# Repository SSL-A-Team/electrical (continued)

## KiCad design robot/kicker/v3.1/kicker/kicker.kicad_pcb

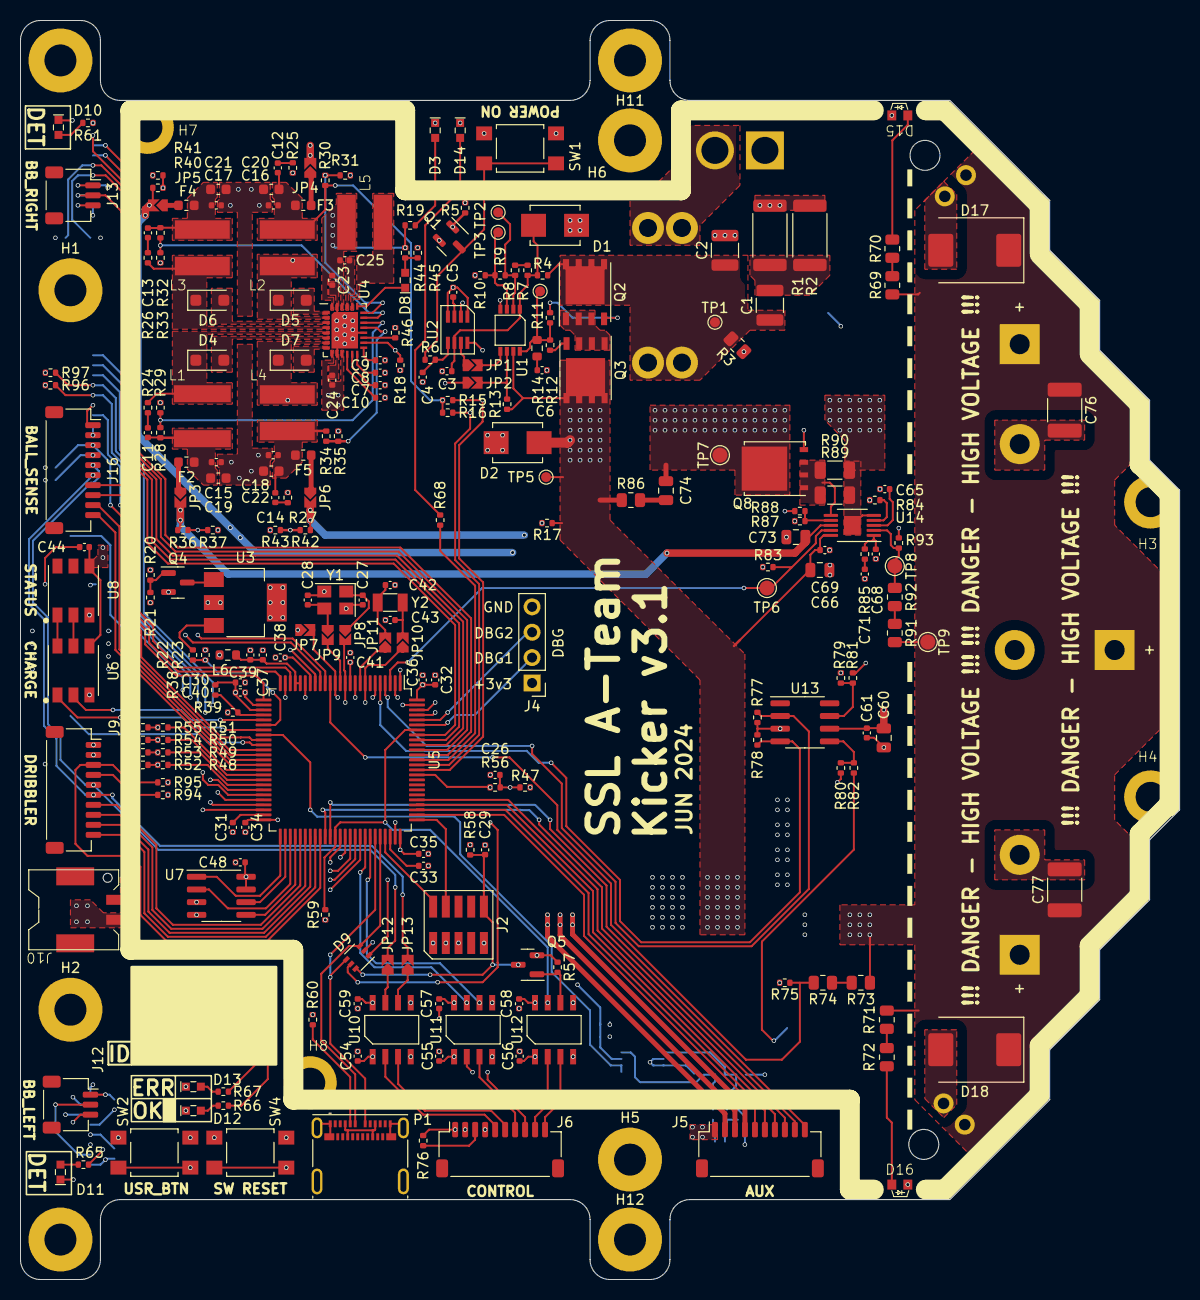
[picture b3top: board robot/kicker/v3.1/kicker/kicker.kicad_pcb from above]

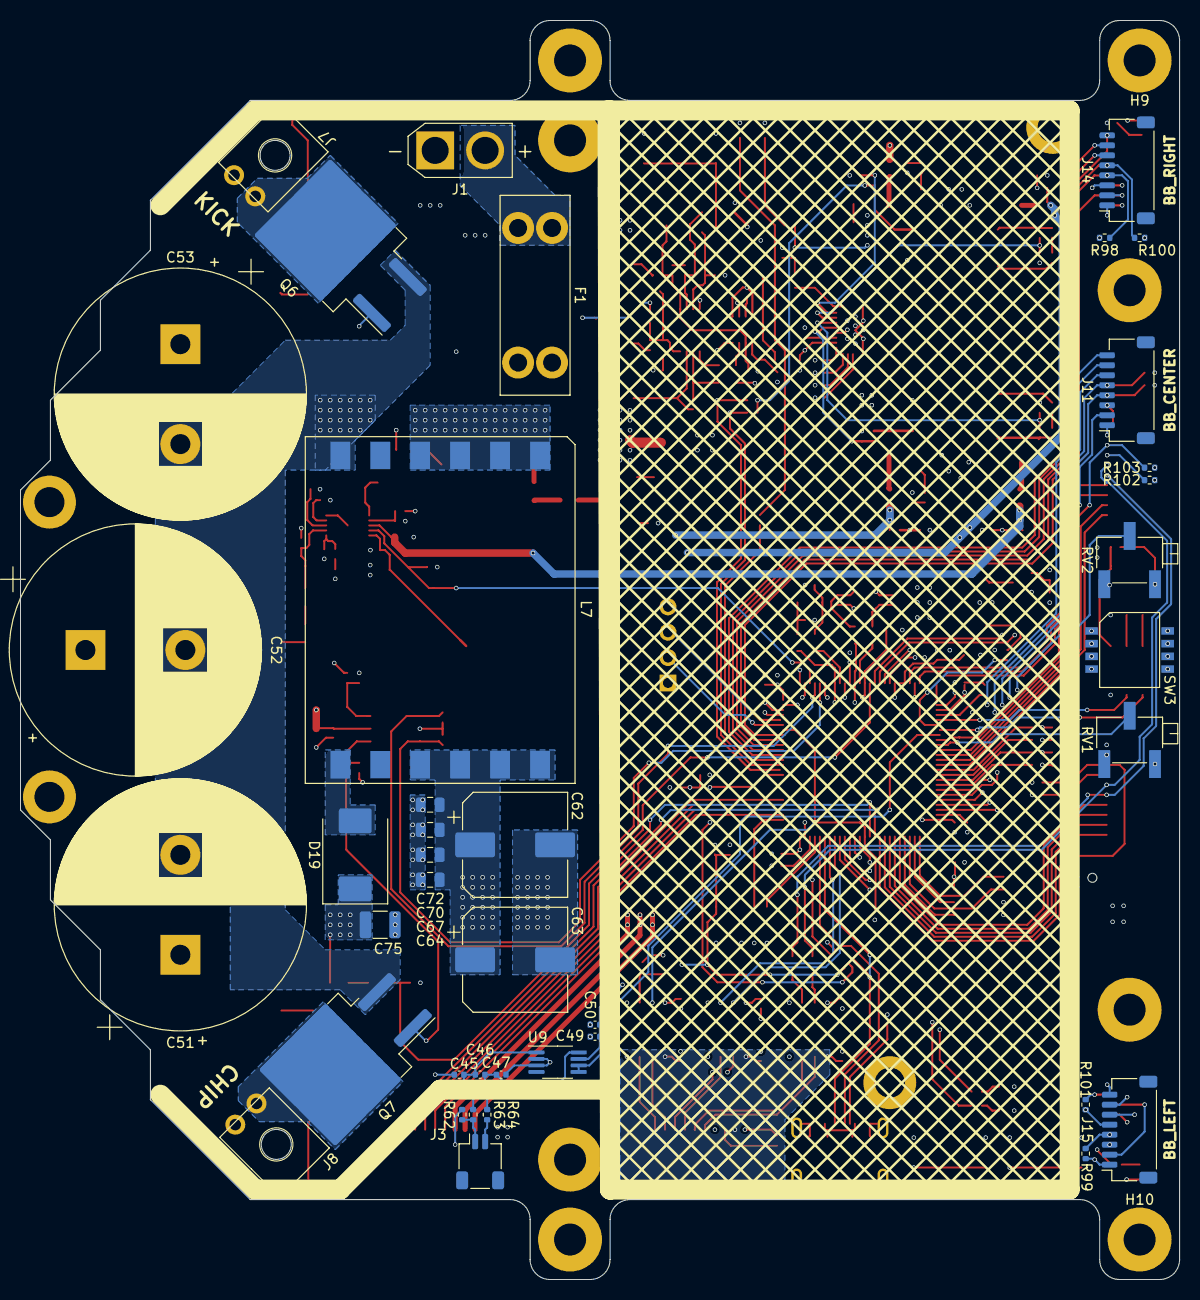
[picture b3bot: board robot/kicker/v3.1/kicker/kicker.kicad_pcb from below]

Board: 6 copper layers, 116.0 x 126.0 mm, 292 parts (40 on the bottom side), 203 nets.

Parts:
C1: 10u 100V; C_1210_3225Metric
C2: 10u 63V; C_1210_3225Metric
C3, C4, C5, C26, C29, C34, C35, C36, C37, C38, C40, C41, C46, C48, C49, C54, C55, C56, C57, C58, C59, C61, C68, C69: 100n 50V; C_0402_1005Metric
C6: 4.7n 63V; C_0402_1005Metric
C7, C8, C45, C47: 10n 6.3V; C_0402_1005Metric
C9, C10: 470n 6.3V; C_0402_1005Metric
C11, C12, C13, C14: 1n 50V; C_0402_1005Metric
C15, C16, C17, C18, C23, C24, C25, C39: 1u 50V; C_0402_1005Metric
C19, C20, C21, C22: 10u 25V; C_0603_1608Metric
C27, C28: 11pF; C_0402_1005Metric
C30, C31, C32, C33, C44: 4.7u 6.3V; C_0402_1005Metric
C42, C43: 15pF; C_0402_1005Metric
C50: 10u 6.3V; C_0402_1005Metric
C51, C52, C53: 1000uF 200V; CP_Radial_D25.0mm_P10.00mm_SnapIn
C60, C64, C66, C67, C70, C72: 10u 50V; C_0805_2012Metric
C62, C63: 220u 50V; CP_Elec_10x10
C65: 10n 50V; C_0402_1005Metric
C71: 6.8n 50V; C_0402_1005Metric
C73: 4.7u 50V; C_0805_2012Metric
C74: 100n 200V; C_0805_2012Metric
C75: 100n 500V; C_1210_3225Metric
C76, C77: 470n 500V; C_1812_4532Metric
D1, D2: 824521261; D_SMB_Non-Polar
D3: XL-1608UWC-04; LED0603
D4, D5, D6, D7: DSS14U; D_SOD-123F
D8, D13: Red; LED0603
D9: PESD3V3L5UY; SOT-363_SC-70-6
D10, D11: Blue; LED0603
D12: Green; LED0603
D14: XL-1608UOC-06; LED0603
D15, D16: Red; APA1606
D17, D18: MURS460; D_SMC
D19: HS5M; D_SMC
F1: 15A; 3557-2
F2, F3, F4, F5: 1.0A; Fuse_0603_1608Metric
H1, H2, H5, H6, H9, H10, H11, H12: M3; MountingHole_3.2mm_M3_Pad
H3, H4, H7, H8: 9774005243R; WE-9774005243R
J1: XT30-F; AMASS_XT30U-M_1x02_P5.0mm_Vertical
J2: Conn_ARM_JTAG_SWD_10; Samtec-2x5pin-0.5mm
J3: Conn_01x02; JST_SH_SM02B-SRSS-TB_1x02-1MP_P1.00mm_Horizontal
J4: Conn_01x04_Pin; PinHeader_1x04_P2.54mm_Vertical
J5, J6, J9, J16: Conn_01x10; JST_SH_SM10B-SRSS-TB_1x10-1MP_P1.00mm_Horizontal
J7, J8: Conn_01x02; 2157601002
J10: Conn_01x02; SM02B-PASS-TBT
J11, J14, J15: Conn_01x08; JST_SH_SM08B-SRSS-TB_1x08-1MP_P1.00mm_Horizontal
J12, J13: Conn_01x03; JST_SH_SM03B-SRSS-TB_1x03-1MP_P1.00mm_Horizontal
JP1: BTN_EN; SolderJumper-2_2.0x1.2mm_Closed
JP2: PWR_EN; SolderJumper-2_2.0x1.2mm_Closed
JP3: 12v0 EN; SolderJumper-2_2.0x1.2mm_Open
JP4: 3v3 EN; SolderJumper-2_2.0x1.2mm_Open
JP5: 5v0 EN; SolderJumper-2_2.0x1.2mm_Open
JP6: 6v2 EN; SolderJumper-2_2.0x1.2mm_Open
JP7: Disable Micro; SolderJumper-2_2.0x1.2mm_Open
JP8, JP9: 8MHZ_CLK_LOCAL; SolderJumper-2_2.0x1.2mm_Closed
JP10, JP11: 32KHZ_CLK_LOCAL; SolderJumper-2_2.0x1.2mm_Closed
JP12: 8MHZ_CLK_EXT; SolderJumper-2_2.0x1.2mm_Closed
JP13: 32KHZ_CLK_EXT; SolderJumper-2_2.0x1.2mm_Closed
L1: ASPI-6045S-220M-T; ASPI-6045S
L2, L3, L4, L5: SDCHA1V5040-150-R; SDCHA1V50
L6: 650 @100MHz; R_0603_1608Metric
L7: GA3460-BL; GA34XX-BL
P1: USB_C_Plug_USB2.0; USB_C_Receptacle_Molex_105450-0101
Q1: BSS138; SOT-23
Q2, Q3: SQJA80EP-T1_GE3; PowerPAK_SO-8L_Single
Q4: SI2310-TP; SOT-23
Q5: BSS138K; SOT-23
Q6, Q7: IXGA48N60A3; TO-263-2
Q8: BSC0402NSATMA1; TDSON-8-1
R1, R2: 1; R_2512_6332Metric
R3, R69, R70, R71, R72: 1.47M; R_0805_2012Metric
R4, R6, R83: 1k; R_0402_1005Metric
R5, R13, R23, R47, R52, R53, R54, R55, R58, R59, R61, R63, R64, R65, R66, R67, R68, R77, R78, R94, R95, R102, R103: 10k; R_0402_1005Metric
R7: 10M; R_0402_1005Metric
R8, R15, R16: 1.5M; R_0402_1005Metric
R9: 69.8k; R_0402_1005Metric
R10: 232k; R_0402_1005Metric
R11, R12, R20, R81, R82, R88: 10; R_0402_1005Metric
R14: 5.1k; R_0603_1608Metric
R17, R18, R57, R79, R80, R87: 100k; R_0402_1005Metric
R19, R38: 23.2k 1%; R_0402_1005Metric
R21: 4.7k; R_0402_1005Metric
R22: 210k; R_0402_1005Metric
R24, R25, R26, R27: 1k 1%; R_0402_1005Metric
R28, R84: 140k 1%; R_0402_1005Metric
R29, R31, R33, R35, R37, R39, R41, R43: 10k 1%; R_0402_1005Metric
R30: 31.6k 1%; R_0402_1005Metric
R32: 53.6k 1%; R_0402_1005Metric
R34: 68.1k 1%; R_0402_1005Metric
R36: 110k 1%; R_0402_1005Metric
R40: 40.2k 1%; R_0402_1005Metric
R42: 52.3k 1%; R_0402_1005Metric
R44, R45, R60: 5.1k; R_0402_1005Metric
R46: 10.7k 1%; R_0402_1005Metric
R48, R49, R50, R51, R56, R76: 330; R_0402_1005Metric
R62: 1M; R_0402_1005Metric
R73, R74: 475k; R_0805_2012Metric
R75: 4.75k; R_0402_1005Metric
R85: 22k 1%; R_0402_1005Metric
R86: 1; R_0805_2012Metric
R89, R90: 4m 1%; R_1206_3216Metric
R91, R92: 976k 0.1%; R_0805_2012Metric
R93: 17.4k 0.1%; R_0402_1005Metric
R96, R97, R98, R99, R100, R101: 2.1k; R_0402_1005Metric
RV1: ACFG1; Potentiometer_Bourns_3269X_Horizontal
RV2: ACFG2; Potentiometer_Bourns_3269X_Horizontal
SW1: PWR_ON; SW_SPST_TL3305A
SW2: BTN0; SW_SPST_TL3305A
SW3: SW_DIP_x04; CHP-041TB
SW4: RST; SW_SPST_TL3305A
TP1: VBatt EOS; TestPoint_Pad_D1.0mm
TP2: LTC4367 UV EOS; TestPoint_Pad_D1.0mm
TP3: LTC4367 OV EOS; TestPoint_Pad_D1.0mm
TP4: Gate SS; TestPoint_Pad_D1.0mm
TP5: VBatt Sys; TestPoint_Pad_D1.0mm
TP6: CHG_EN; TestPoint_Pad_D1.5mm
TP7: SPICE: V_{drain} <<<HIGH VOLTAGE>>>; TestPoint_Pad_D1.5mm
TP8: FB; TestPoint_Pad_D1.5mm
TP9: SPICE: V_{out} <<<HIGH VOLTAGE>>>; TestPoint_Pad_D1.5mm
U1: LTC4367; MS8
U2: LTC2955-1; LTC2955-TS8
U3: ITS4140N; SOT-223
U4: LT3504; UFD
U5: STM32F407VETx; LQFP-100_14x14mm_P0.5mm
U6, U8: SK9822
U7: AT25DF041x-UxN-x; SOIC-8_3.9x4.9mm_P1.27mm
U9: AD8494; MSOP-8_3x3mm_P0.65mm
U10, U12: ISO6720-Q1; ISO672X
U11: ISO6721-Q1; ISO672X
U13: IX4427; SOIC-8_3.9x4.9mm_P1.27mm
U14: LT3757EMSE; MSOP-10-1EP_3x3mm_P0.5mm_EP1.68x1.88mm
Y1: TAXM8M4RDBCCT2T; Crystal_SMD_3225-4Pin_3.2x2.5mm
Y2: Q13FC13500005; Crystal_SMD_3215-2Pin_3.2x1.5mm

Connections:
+3.3V_{PREFUSE}: C12.2, C16.1, C20.1, F3.1, L2.2, R15.1, R16.1, R30.1
+3V3: C30.2, C32.2, C34.1, C35.1, C36.1, C38.1, C40.1, C41.1, C48.2, C49.1, C50.2, C57.1, C58.1, C59.1, J2.1 (VTref), J4.1, J5.2, J9.2, J11.1, J12.1, J13.1, J14.1, J15.1, J16.2, JP4.2 (B), L6.1, R20.2, R38.1, R58.1, R94.1, R95.1, R96.1, R97.1, R98.1, R99.1, R100.1, R101.1, R102.1, R103.1, RV1.1, RV2.1, SW2.2, SW3.5, SW3.6, SW3.7, SW3.8, U5.6 (VBAT), U5.11 (VDD), U5.19 (VDD), U5.28 (VDD), U5.50 (VDD), U5.75 (VDD), U5.100 (VDD), U7.3 (~WP/IO2), U7.7 (~HOLD/IO3), U7.8 (VCC), U9.7 (+Vs), U10.8 (VCC2), U11.8 (VCC2), U12.8 (VCC2)
+5V: C44.2, J5.3, JP5.2 (B), R40.1, U6.4 (VCC), U8.4 (VCC)
+6V: J5.4, JP6.2 (B), R42.1
+12V: C60.1, C61.1, C73.1, JP3.2 (B), R36.1, U13.6 (V+), U14.8 (INTVCC)
+BATT: C23.1, C24.1, C25.2, C62.1, C63.1, C64.1, C66.1, C67.1, C69.1, C70.1, C72.1, D2.2 (A2), J10.1, L5.2, L7.9, L7.10, L7.11, L7.12, Q3.5 (D), R13.1, R17.1, R19.1, R44.1, R86.1, TP5.1, U1.7 (V_{OUT}), U3.2 (V_{bb}), U3.4 (V_{bb}), U4.9 (V_{IN}), U4.11 (V_{IN}), U4.26 (V_{IN}), U4.28 (V_{IN}), U14.10 (VIN)
/Ball Sense/8MHZ_CLK_REF: J9.5, J16.5, JP8.2 (B), JP12.2 (B), U5.12 (PH0)
/Ball Sense/32KHZ_CLK_REF: J9.6, J16.6, JP10.1 (A), JP13.2 (B), U5.8 (PC14)
/Ball Sense/SENSE_BOOT_UART.BOOT0: J16.9, U5.38 (PE7)
/Ball Sense/SENSE_BOOT_UART.RST: J16.10, U5.39 (PE8)
/Ball Sense/SENSE_BOOT_UART.RX: J16.8, U5.26 (PA3)
/Ball Sense/SENSE_BOOT_UART.TX: J16.7, U5.25 (PA2)
/Ball Sense/SENSE_BOOT_UART.~DET: J16.3, R103.2, U5.37 (PB2)
/Breakbeam/BB_CENTER.AGPIO: J11.2, U5.34 (PC5)
/Breakbeam/BB_CENTER.INT: J11.8, U5.46 (PE15)
/Breakbeam/BB_CENTER.RST: J11.6, U5.45 (PE14)
/Breakbeam/BB_CENTER.SCL: J11.5, R97.2, U5.47 (PB10)
/Breakbeam/BB_CENTER.SDA: J11.4, R96.2, U5.48 (PB11)
/Breakbeam/BB_CENTER.~DET: J11.7, U5.44 (PE13)
/Breakbeam/BB_LEFT.AGPIO: J12.2, J15.2, U5.24 (PA1)
/Breakbeam/BB_LEFT.INT: J15.8, U5.65 (PC8)
/Breakbeam/BB_LEFT.RST: J15.6, U5.64 (PC7)
/Breakbeam/BB_LEFT.SCL: J15.5, R101.2, U5.67 (PA8)
/Breakbeam/BB_LEFT.SDA: J15.4, R99.2, U5.66 (PC9)
/Breakbeam/BB_LEFT.~DET: J15.7, U5.63 (PC6)
/Breakbeam/BB_RIGHT.AGPIO: J13.2, J14.2, U5.23 (PA0)
/Breakbeam/BB_RIGHT.INT: J14.8, U5.91 (PB5)
/Breakbeam/BB_RIGHT.RST: J14.6, U5.90 (PB4)
/Breakbeam/BB_RIGHT.SCL: J14.5, R100.2, U5.92 (PB6)
/Breakbeam/BB_RIGHT.SDA: J14.4, R98.2, U5.93 (PB7)
/Breakbeam/BB_RIGHT.~DET: J14.7, U5.89 (PB3)
/Dribbler/DRIB_BOOT_UART.BOOT0: J9.9, U5.57 (PD10)
/Dribbler/DRIB_BOOT_UART.RST: J9.10, U5.58 (PD11)
/Dribbler/DRIB_BOOT_UART.RX: J9.8, U5.56 (PD9)
/Dribbler/DRIB_BOOT_UART.TX: J9.7, U5.55 (PD8)
/Dribbler/DRIB_BOOT_UART.~DET: J9.3, R95.2, U5.59 (PD12)
/Power Protection/PGOOD_{VBATT}: JP2.1 (A), R18.1, U4.16 (EN/UVLO)
/Power Protection/V_{BATT}: F1.1, J1.2
/Power Protection/V_{BATT}_FUSED: C1.1, C2.1, F1.2, Q2.5 (D), R3.2, R4.2, TP1.1
/digital/AUX_GPIO1: J5.9, U5.60 (PD13)
/digital/AUX_GPIO2: J5.10, U5.61 (PD14)
/digital/AUX_MISO: J5.7, U5.79 (PC11)
/digital/AUX_MOSI: J5.8, U5.80 (PC12)
/digital/AUX_NSS: J5.5, U5.77 (PA15)
/digital/AUX_SCK: J5.6, U5.78 (PC10)
/digital/BB_LED1_BLUE: R61.1, U5.1 (PE2)
/digital/BB_LED2_BLUE: R65.1, U5.2 (PE3)
/digital/CMD_{CHG}: R83.1, TP6.1, U5.3 (PE4), U14.9 (~SHDN/UVLO)
/digital/CMD_{CHIP}: R78.1, U5.5 (PE6), U13.4 (INB)
/digital/CMD_{KICK}: R77.1, U5.4 (PE5), U13.2 (INA)
/digital/DBG_HDR1: J4.2, U5.95 (PB8)
/digital/DBG_HDR2: J4.3, U5.96 (PB9)
/digital/DIP0: R51.2, U5.40 (PE9)
/digital/DIP1: R50.2, U5.41 (PE10)
/digital/DIP2: R49.2, U5.42 (PE11)
/digital/DIP3: R48.2, U5.43 (PE12)
/digital/DOTSTAR_MOSI: U5.32 (PA7), U6.1 (SDI)
/digital/DOTSTAR_SCK: U5.30 (PA5), U6.2 (CKI)
/digital/FLASH_MISO: U5.53 (PB14), U7.2 (SO/IO1)
/digital/FLASH_MOSI: U5.54 (PB15), U7.5 (SI/IO0)
/digital/FLASH_NSS: U5.51 (PB12), U7.1 (~CS)
/digital/FLASH_SCK: U5.52 (PB13), U7.6 (SCK)
/digital/LED_GREEN: R66.1, U5.97 (PE0)
/digital/LED_RED: R67.1, U5.98 (PE1)
/digital/MCU_BOOT_UART.BOOT0: R59.2, U5.62 (PD15), U5.94 (BOOT0), U12.7 (OUTA)
/digital/MCU_BOOT_UART.PWR_EN: J6.4, Q1.1 (G), R5.2
/digital/MCU_BOOT_UART.RST: Q5.1 (G), R57.1, U12.6 (OUTB)
/digital/MCU_BOOT_UART.RX: U5.69 (PA10), U11.6 (OUTB)
/digital/MCU_BOOT_UART.TX: U5.68 (PA9), U11.7 (INA)
/digital/MCU_BOOT_UART.~DET: J6.3, R76.2
/digital/NRST: C29.1, D9.6 (K5), J2.10 (~RESET), JP7.2 (B), Q5.3 (D), R58.2, SW4.2, U5.14 (NRST)
/digital/PWR_BTN_PRESSED_~INT: R15.2, U2.8 (~INT), U5.86 (PD5)
/digital/PWR_KILL: R16.2, U2.2 (~KILL), U5.87 (PD6)
/digital/SWCLK: J2.4 (SWDCLK/TCK), U5.76 (PA14)
/digital/SWDIO: J2.2 (SWDIO/TMS), U5.72 (PA13)
/digital/ShutdownInitiated: R68.1, U5.88 (PD7)
/digital/TEMP_PROBE: U5.33 (PC4), U9.5 (SENSE), U9.6
/digital/USB_OTG_FS_D_N: D9.4 (K3), P1.A7 (D-), U5.70 (PA11)
/digital/USB_OTG_FS_D_P: D9.3 (K2), P1.A6 (D+), U5.71 (PA12)
/digital/USER_ADJ1: RV1.2, U5.35 (PB0)
/digital/USER_ADJ2: RV2.2, U5.36 (PB1)
/digital/USR_BTN: D9.5 (K4), R56.1, U5.85 (PD4)
/digital/V_{sense}_3v3: R38.2, R39.1, U5.29 (PA4)
/digital/V_{sense}_5v0: R40.2, R41.1, U5.17 (PC2)
/digital/V_{sense}_6v2: R42.2, R43.1, U5.18 (PC3)
/digital/V_{sense}_12v0: R36.2, R37.1, U5.16 (PC1)
/digital/V_{sense}_HV: D9.1 (K1), R74.2, R75.1, U5.15 (PC0)
/digital/V_{sense}_V_{batt}: R22.2, R23.1, U5.31 (PA6)
/hv_kicker/DL1S: R69.2, R70.1
/hv_kicker/DL2S: R71.2, R72.1
/hv_kicker/HVMS: R73.2, R74.1
/hv_kicker/flyback_charger/CSP: Q8.1 (S), Q8.2 (S), Q8.3 (S), R89.2, R90.2, U14.6 (SENSE)
/hv_kicker/flyback_charger/FB: R92.1, R93.2, TP8.1, U14.2 (FBX)
/hv_kicker/flyback_charger/HVFBS: R91.1, R92.2
/hv_kicker/flyback_charger/HVGATE: R87.2, R88.1, U14.7 (GATE)
/hv_kicker/flyback_charger/HV_AC: D19.2 (A), L7.7
/hv_kicker/flyback_charger/V_{solenoid}: C51.1, C52.1, C53.1, C75.1, C76.1, C77.1, D17.1 (K), D18.1 (K), D19.1 (K), J7.1, J8.2, R69.1, R71.1, R73.1, R91.2, TP9.1
/hv_kicker/flyback_charger/V_{trans}: C74.2, L7.1, L7.2, L7.3, L7.4, Q8.5 (D), TP7.1
/hv_kicker/solenoid_control/CHIP_SW: D18.2 (A), J8.1, Q7.2 (C)
/hv_kicker/solenoid_control/GATE_{chip}: R80.1, R82.1, U13.5 (OUTB)
/hv_kicker/solenoid_control/GATE_{chip}_FILT: Q7.1 (G), R82.2
/hv_kicker/solenoid_control/GATE_{kick}: R79.1, R81.1, U13.7 (OUTA)
/hv_kicker/solenoid_control/GATE_{kick}_FILT: Q6.1 (G), R81.2
/hv_kicker/solenoid_control/KICK_SW: D17.2 (A), J7.2, Q6.2 (C)
/isol/BOOT_UART_BOOT0_ISOL: J6.9, U12.2 (INA)
/isol/BOOT_UART_RST_ISOL: J6.10, U12.3 (INB)
/isol/BOOT_UART_RX_ISOL: J6.7, U11.3 (INB)
/isol/BOOT_UART_TX_ISOL: J6.8, U11.2 (OUTA)
/isol/CLK_8M_ISOL: J6.5, U10.2 (INA)
/isol/CLK_32K_ISOL: J6.6, U10.3 (INB)
/isol/GND_ISOL: C54.2, C55.2, C56.2, J6.1, R76.1, U10.4 (GND1), U11.4 (GND1), U12.4 (GND1)
/isol/V_{logic}_ISOL: C54.1, C55.1, C56.1, J6.2, U10.1 (VCC1), U11.1 (VCC1), U12.1 (VCC1)
GND: C2.2, C3.2, C4.2, C5.2, C6.2, C7.2, C8.2, C9.2, C10.2, C15.2, C16.2, C17.2, C18.2, C19.2, C20.2, C21.2, C22.2, C23.2, C24.2, C26.2, C27.2, C28.2, C29.2, C30.1, C31.1, C32.1, C33.1, C34.2, C35.2, C36.2, C37.2, C38.2, C39.2, C40.2, C41.2, C42.2, C43.2, C44.1, C45.1, C47.2, C48.1, C49.2, C50.1, C51.2, C52.2, C53.2, C57.2, C58.2, C59.2, C60.2, C61.2, C62.2, C63.2, C64.2, C65.2, C66.2, C67.2, C68.2, C69.2, C70.2, C71.2, C72.2, C73.2, C75.2, C76.2, C77.2, D1.1 (A1), D2.1 (A1), D3.1 (K), D9.2 (A), D10.1 (K), D11.1 (K), D12.1 (K), D13.1 (K), D14.1 (K), D15.1 (K), D16.1 (K), J1.1, J2.3 (GND), J2.5 (GND), J2.9 (GNDDetect), J4.4, J5.1, J9.1, J10.2, J11.3, J12.3, J13.3, J14.3, J15.3, J16.1, JP7.1 (A), L7.6, P1.A1 (GND), P1.A12 (GND), P1.B1 (GND), P1.B12 (GND), P1.S1 (SHIELD), Q1.2 (S), Q4.2 (S), Q5.2 (S), Q6.3 (E), Q7.3 (E), R1.2, R2.2, R3.1, R5.1, R10.1, R17.2, R18.2, R21.2, R23.2, R29.2, R31.2, R33.2, R35.2, R37.2, R39.2, R41.2, R43.2, R45.1, R46.2, R47.2, R52.1, R53.1, R54.1, R55.1, R57.2, R59.1, R60.2, R62.1, R75.2, R77.2, R78.2, R79.2, R80.2, R83.2, R84.1, R87.1, R89.1, R90.1, R93.1, RV1.3, RV2.3, SW1.1, SW4.1, U1.4 (GND), U2.1 (ON), U2.4 (GND), U4.10 (GND), U4.18 (GND), U4.27 (GND), U4.29 (GND), U5.10 (VSS), U5.20 (VSSA), U5.27 (VSS), U5.74 (VSS), U5.99 (VSS), U6.3 (GND), U7.4 (GND), U8.3 (GND), U9.2 (REF), U9.3 (-Vs), U10.5 (GND2), U11.5 (GND2), U12.5 (GND2), U13.3 (GND), U14.5 (SYNC), U14.11 (GND), Y1.2, Y1.4
unnamed: C1.2, R1.1, R2.1
unnamed: C6.1, R14.2
unnamed: C11.1, R24.2
unnamed: C11.2, C15.1, C19.1, F2.1, L1.2, R28.1
unnamed: C12.1, R25.2
unnamed: C13.1, R26.2
unnamed: C13.2, C17.1, C21.1, F4.1, L3.2, R32.1
unnamed: C14.1, R27.2
unnamed: C14.2, C18.1, C22.1, F5.1, L4.2, R34.1
unnamed: C26.1, R47.1, R56.2, SW2.1
unnamed: C71.1, R85.1
unnamed: C74.1, R86.2
unnamed: C3.1, D1.2 (A2), R4.1, R7.1, U1.1 (V_{IN}), U2.6 (V_{in})
unnamed: D3.2 (A), R19.2
unnamed: D4.2 (A), U4.6 (DA1)
unnamed: D4.1 (K), L1.1, R24.1, U4.5 (SW1)
unnamed: D5.2 (A), U4.1 (DA2)
unnamed: D5.1 (K), L2.1, R25.1, U4.2 (SW2)
unnamed: D6.2 (A), U4.3 (DA3)
unnamed: D6.1 (K), L3.1, R26.1, U4.4 (SW3)
unnamed: D7.2 (A), U4.8 (DA4)
unnamed: D7.1 (K), L4.1, R27.1, U4.7 (SW4)
unnamed: D8.2 (A), R44.2, R45.2
unnamed: D8.1 (K), U4.23 (PG)
unnamed: D10.2 (A), R61.2
unnamed: D11.2 (A), R65.2
unnamed: D12.2 (A), R66.2
unnamed: D13.2 (A), R67.2
unnamed: D14.2 (A), R68.2
unnamed: D15.2 (A), R70.2
unnamed: D16.2 (A), R72.2
unnamed: J3.1, R62.2, R63.1
unnamed: J3.2, R64.1
unnamed: J9.4, R94.2
unnamed: J16.4, R102.2
unnamed: JP1.1 (A), U2.7 (EN)
unnamed: JP1.2 (B), U1.5 (~SHDN)
unnamed: JP2.2 (B), R13.2, U1.6 (~FAULT)
unnamed: F2.2, JP3.1 (A)
unnamed: F3.2, JP4.1 (A)
unnamed: F4.2, JP5.1 (A)
unnamed: F5.2, JP6.1 (A)
unnamed: C27.1, JP8.1 (A), Y1.1
unnamed: C28.1, JP9.1 (A), Y1.3
unnamed: JP9.2 (B), U5.13 (PH1)
unnamed: C43.1, JP10.2 (B), Y2.2
unnamed: JP11.1 (A), U5.9 (PC15)
unnamed: C42.1, JP11.2 (B), Y2.1
unnamed: JP12.1 (A), U10.7 (OUTA)
unnamed: JP13.1 (A), U10.6 (OUTB)
unnamed: P1.A5 (CC), R60.1
unnamed: Q1.3 (D), R6.2, SW1.2
unnamed: Q2.4 (G), R11.1
unnamed: Q2.1 (S), Q2.2 (S), Q2.3 (S), Q3.1 (S), Q3.2 (S), Q3.3 (S)
unnamed: Q3.4 (G), R12.2
unnamed: Q4.3 (D), U3.1 (IN)
unnamed: Q4.1 (G), R20.1, R21.1
unnamed: Q8.4 (G), R88.2
unnamed: R7.2, R8.1
unnamed: R48.1, R52.2, SW3.4
unnamed: R49.1, R53.2, SW3.3
unnamed: R50.1, R54.2, SW3.2
unnamed: R51.1, R55.2, SW3.1
unnamed: R11.2, R12.1, R14.1, TP4.1, U1.8 (GATE)
unnamed: R9.2, R10.2, TP3.1, U1.3 (OV)
unnamed: R8.2, R9.1, TP2.1, U1.2 (UV)
unnamed: C5.1, U2.3 (TMR)
unnamed: C4.1, R6.1, U2.5 (~PB)
unnamed: R22.1, U3.3 (OUT)
unnamed: R46.1, U4.17 (RT/SYNC)
unnamed: C25.1, U4.25 (SKY)
unnamed: L5.1, U4.24 (SW5)
unnamed: R28.2, R29.1, U4.20 (FB1)
unnamed: C7.1, U4.13 (RUN/SS1)
unnamed: R30.2, R31.1, U4.22 (FB2)
unnamed: C8.1, U4.14 (RUN/SS2)
unnamed: R32.2, R33.1, U4.21 (FB3)
unnamed: C9.1, U4.15 (RUN/SS3)
unnamed: R34.2, R35.1, U4.19 (FB4)
unnamed: C10.1, U4.12 (RUN/SS4)
unnamed: C31.2, U5.49 (VCAP_1)
unnamed: C33.2, U5.73 (VCAP_2)
unnamed: C37.1, C39.1, L6.2, U5.21 (VREF+), U5.22 (VDDA)
unnamed: U6.5 (CKO), U8.2 (CKI)
unnamed: U6.6 (SDO), U8.1 (SDI)
unnamed: C46.2, C47.1, R64.2, U9.8 (+IN)
unnamed: C45.2, C46.1, R63.2, U9.1 (-IN)
unnamed: R84.2, U14.4 (RT)
unnamed: C65.1, U14.3 (SS)
unnamed: C68.1, R85.2, U14.1 (VC)

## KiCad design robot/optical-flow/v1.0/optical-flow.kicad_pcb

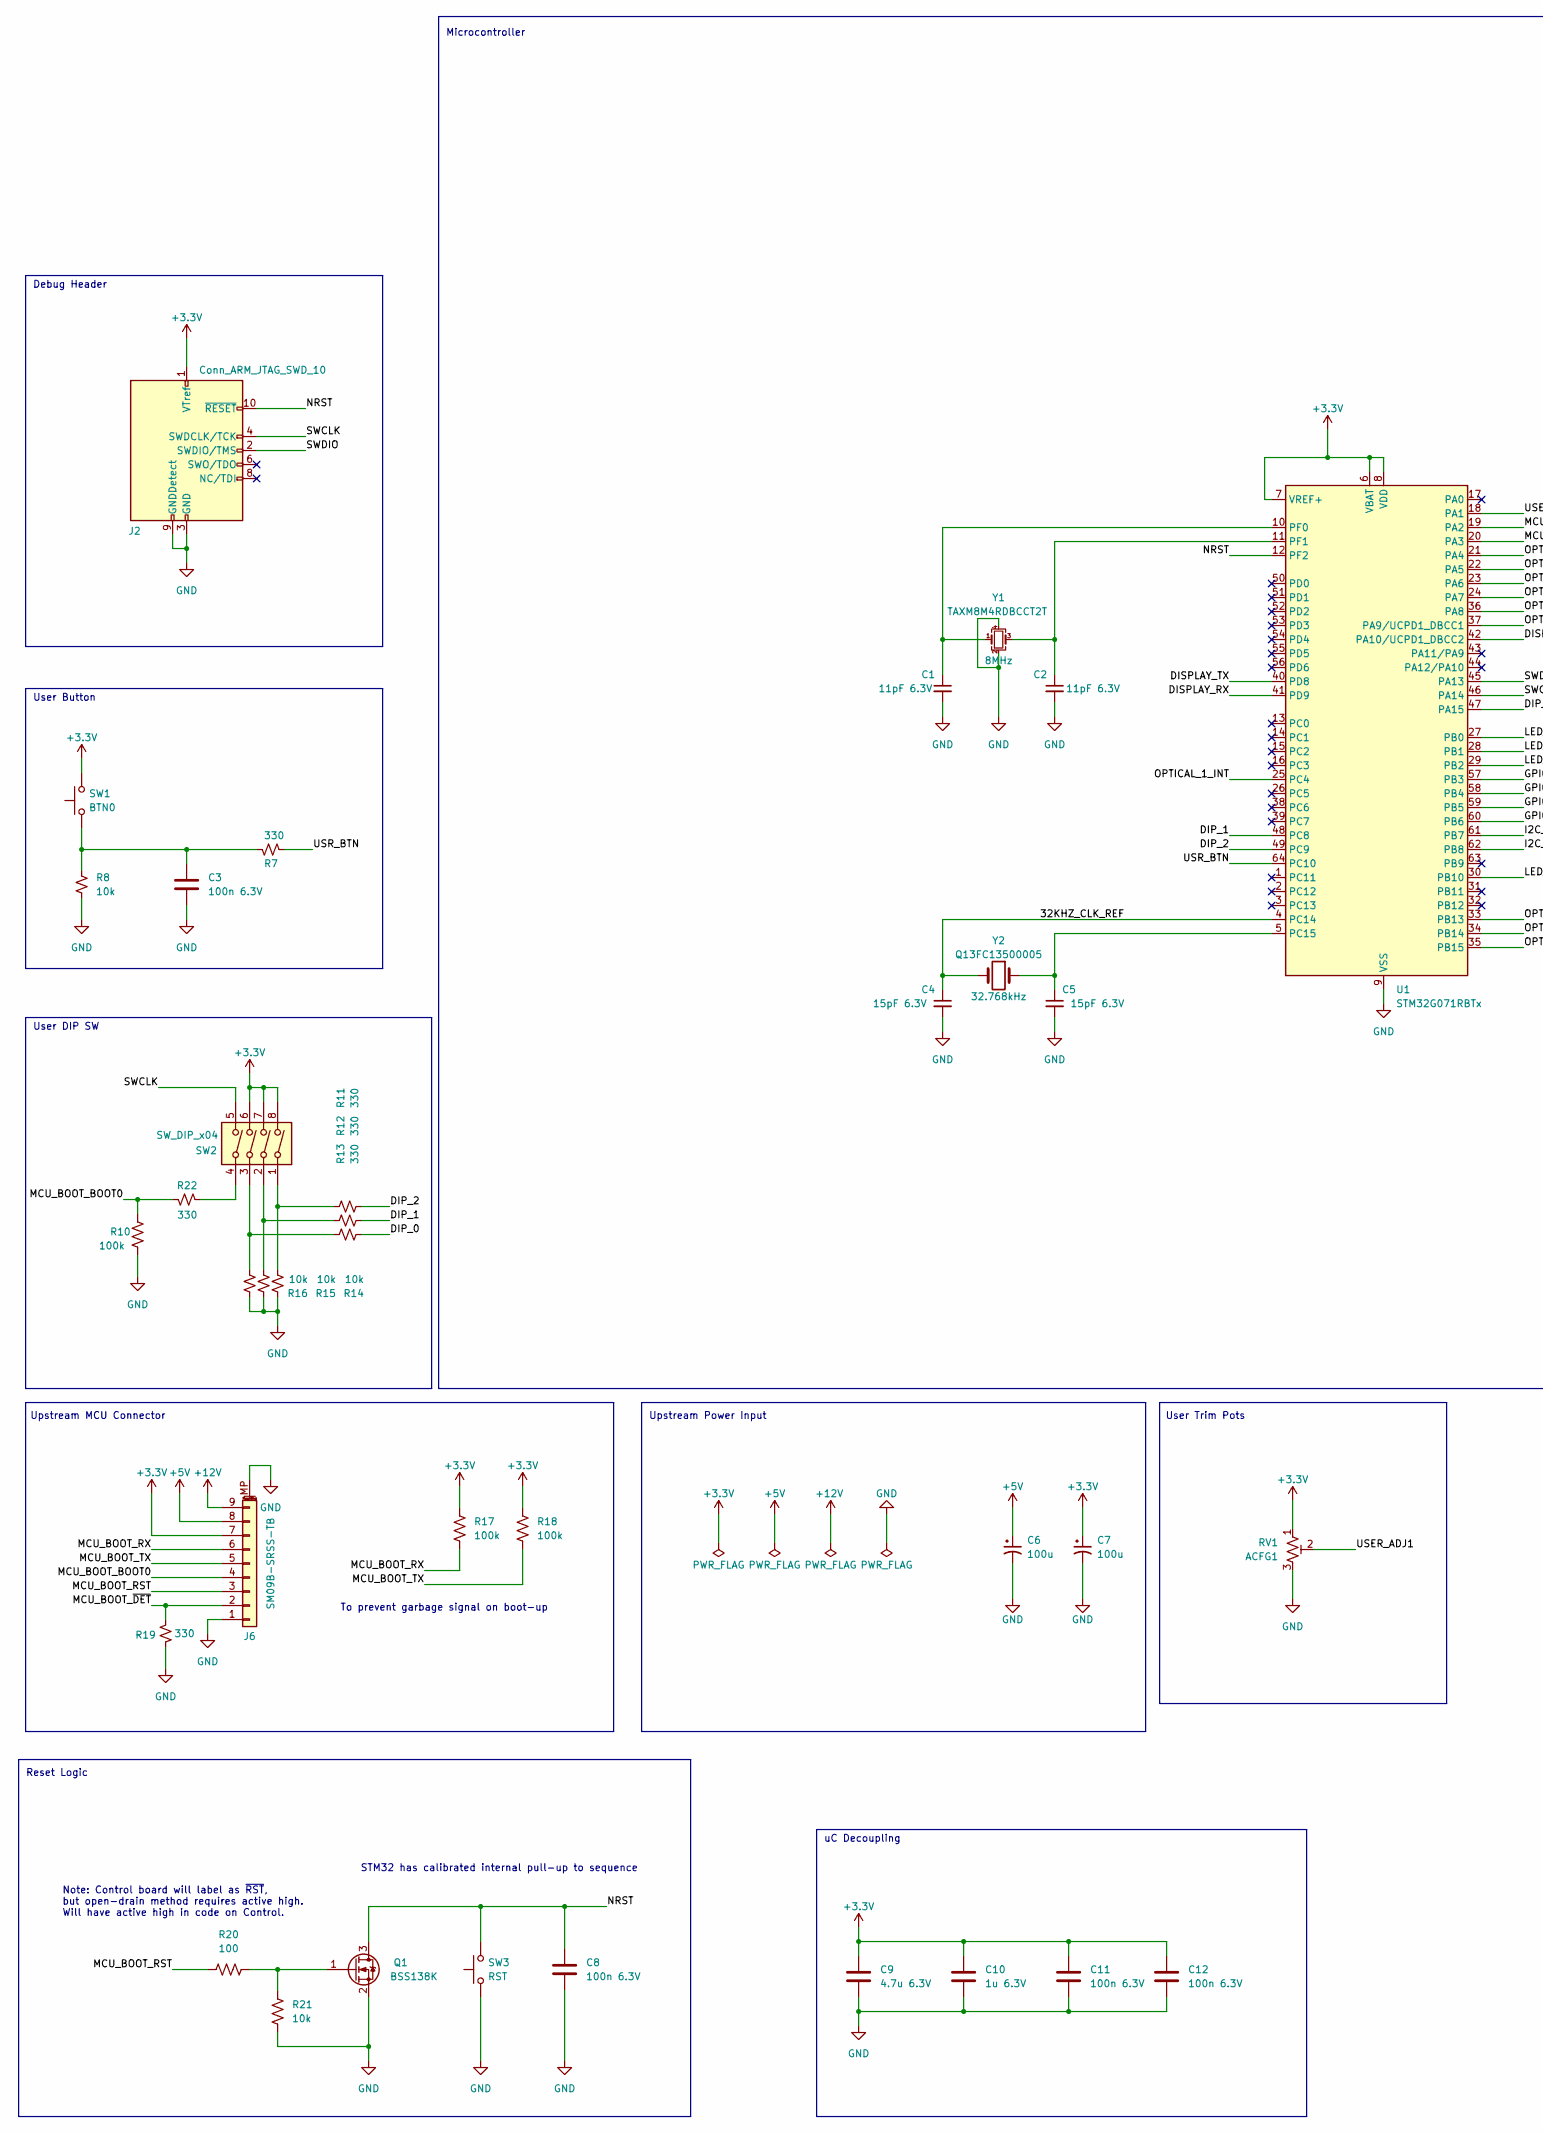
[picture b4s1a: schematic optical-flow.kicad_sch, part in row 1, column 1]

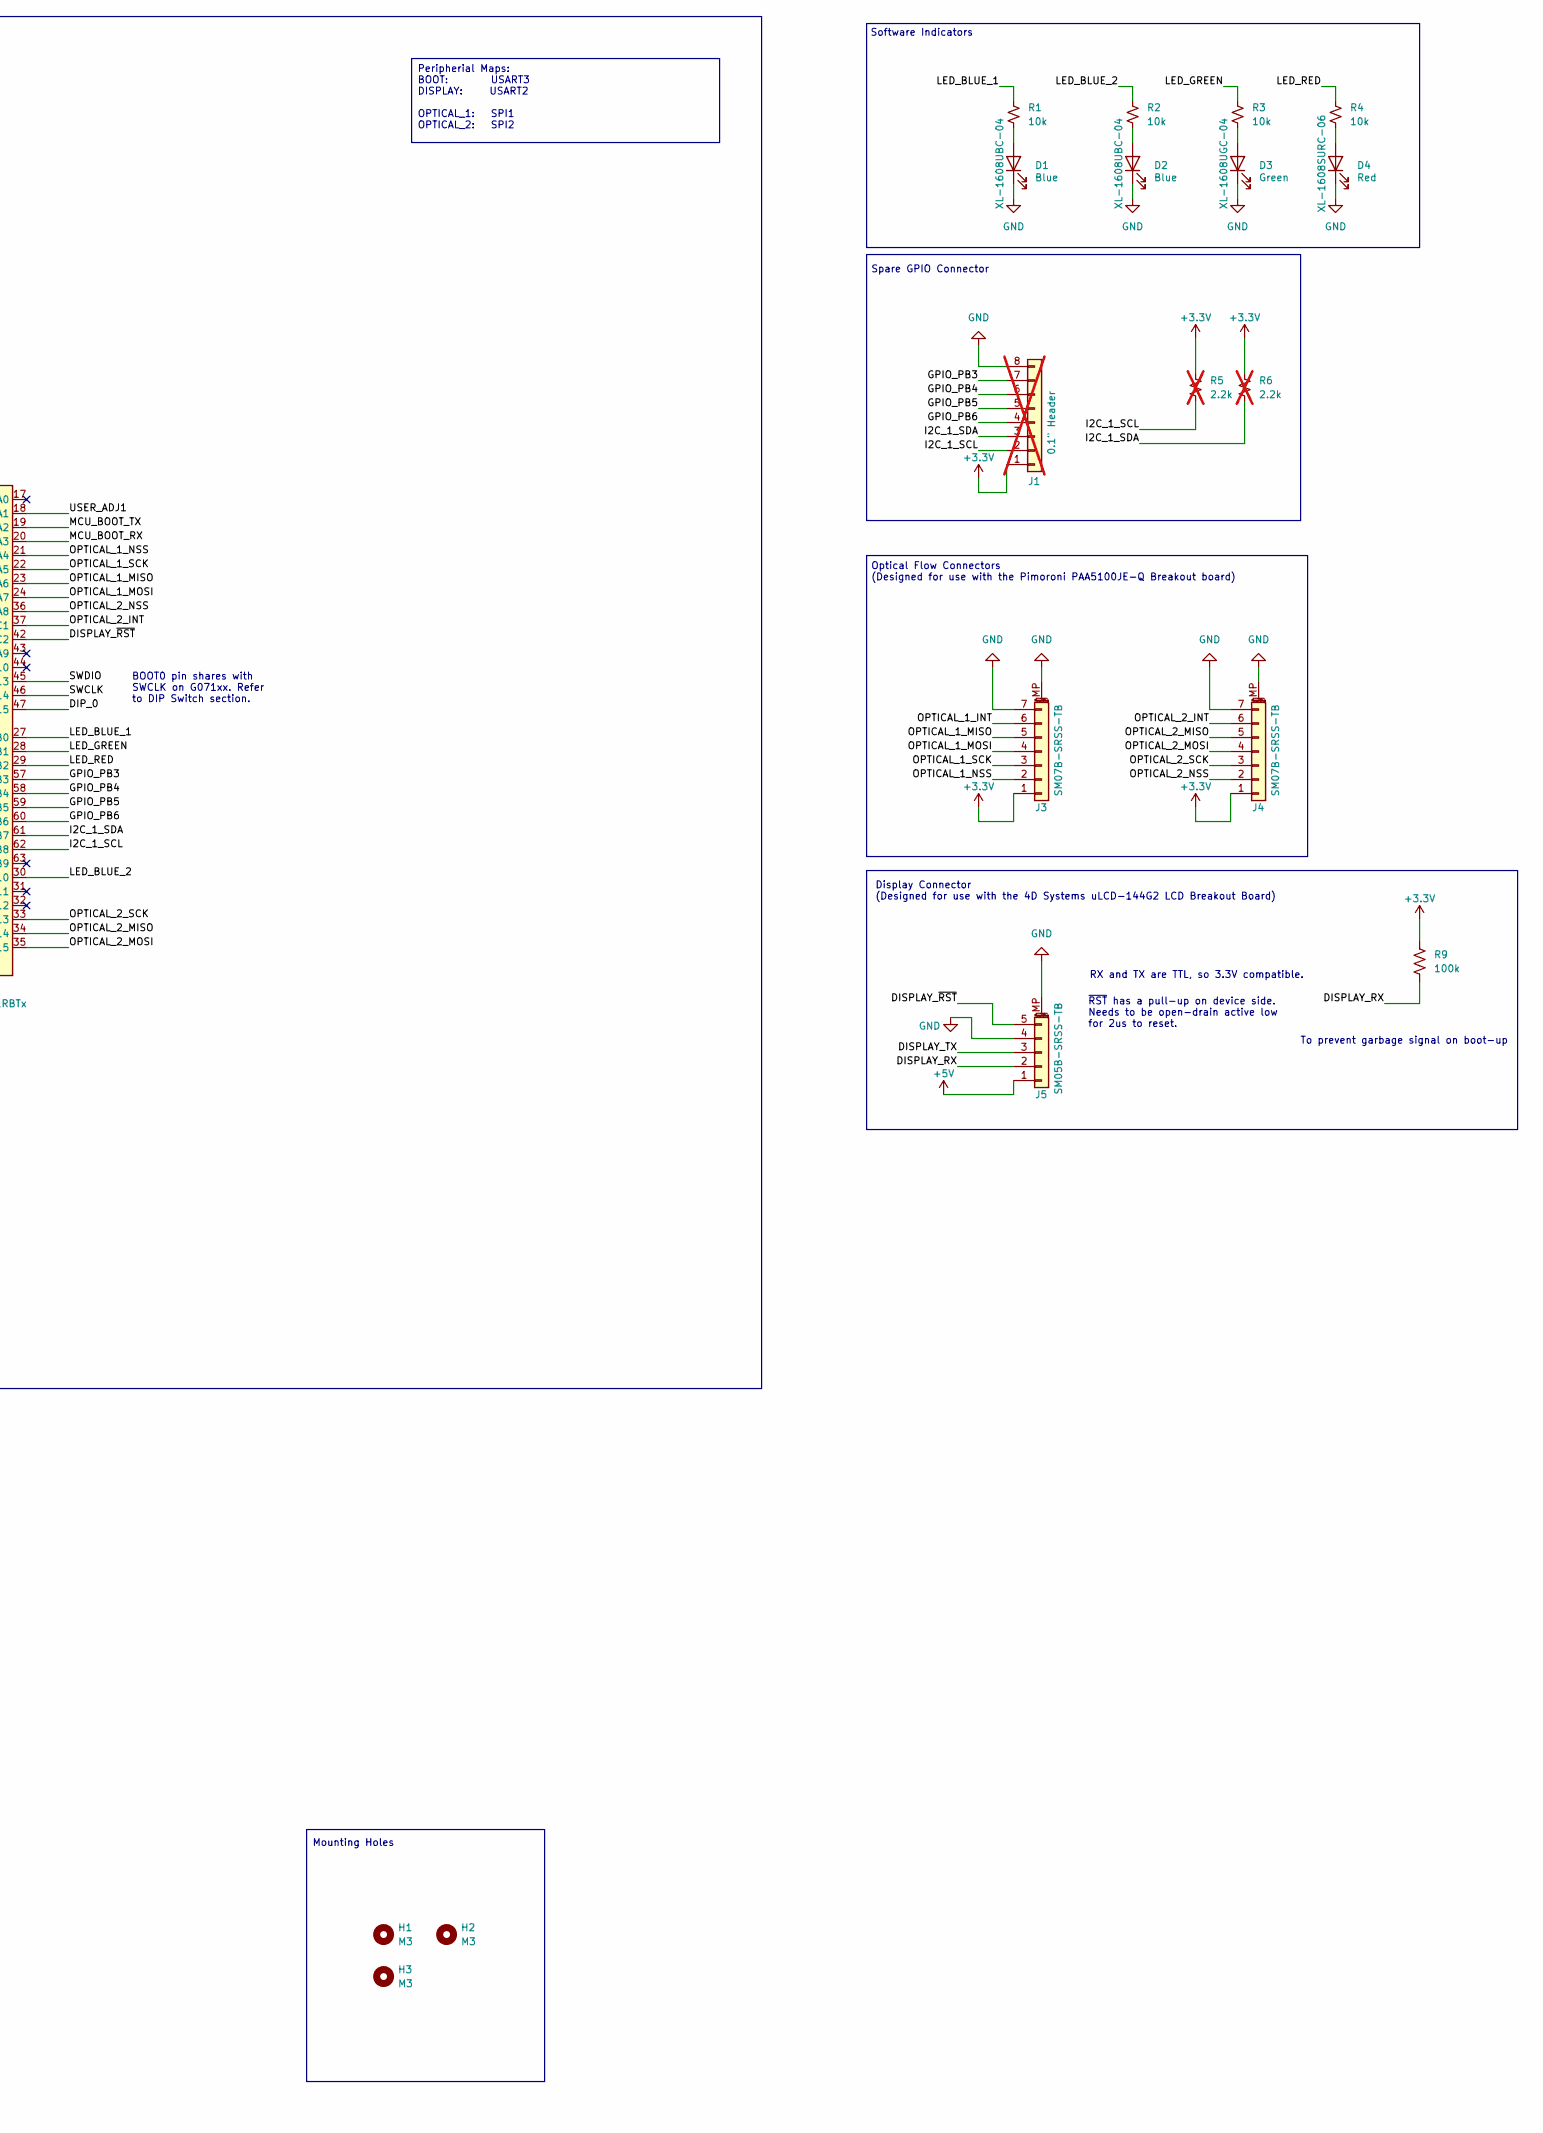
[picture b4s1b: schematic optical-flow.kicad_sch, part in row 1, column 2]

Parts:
C1, C2: 11pF 6.3V; C_0402_1005Metric
C3, C8, C11, C12: 100n 6.3V; C_0402_1005Metric
C4, C5: 15pF 6.3V; C_0402_1005Metric
C6, C7: 100u; CP_Elec_6.3x5.4_Nichicon
C9: 4.7u 6.3V; C_0402_1005Metric
C10: 1u 6.3V; C_0402_1005Metric
D1, D2: XL-1608UBC-04; LED0603
D3: XL-1608UGC-04; LED0603
D4: XL-1608SURC-06; LED0603
H1, H2, H3: M3; MountingHole_3.2mm_M3
J1: 0.1" Header; PinSocket_1x08_P2.54mm_Vertical; not fitted
J2: Conn_ARM_JTAG_SWD_10; Samtec-2x5pin-1.27mm
J3, J4: SM07B-SRSS-TB; JST_SH_SM07B-SRSS-TB_1x07-1MP_P1.00mm_Horizontal
J5: SM05B-SRSS-TB; JST_SH_SM05B-SRSS-TB_1x05-1MP_P1.00mm_Horizontal
J6: SM09B-SRSS-TB; JST_SH_SM09B-SRSS-TB_1x09-1MP_P1.00mm_Horizontal
Q1: BSS138K; SOT-23
R1, R2, R3, R4, R8, R14, R15, R16, R21: 10k; R_0402_1005Metric
R5, R6: 2.2k; R_0402_1005Metric; not fitted
R7, R11, R12, R13, R19, R22: 330; R_0402_1005Metric
R9, R10, R17, R18: 100k; R_0402_1005Metric
R20: 100; R_0402_1005Metric
RV1: ACFG1; Potentiometer_Bourns_3269X_Horizontal
SW1: BTN0; SW_SPST_TL3305A
SW2: SW_DIP_x04; CHP-041TB
SW3: RST; SW_SPST_TL3305A
U1: STM32G071RBTx; LQFP-64_10x10mm_P0.5mm
Y1: TAXM8M4RDBCCT2T; Crystal_SMD_3225-4Pin_3.2x2.5mm
Y2: Q13FC13500005; Crystal_SMD_3215-2Pin_3.2x1.5mm

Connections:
+3.3V: C7.1, C9.2, C10.2, C11.1, C12.1, J1.1, J2.1 (VTref), J3.1, J4.1, J6.7, R5.1, R6.1, R9.1, R17.1, R18.1, RV1.1, SW1.2, SW2.6, SW2.7, SW2.8, U1.6 (VBAT), U1.7 (VREF+), U1.8 (VDD)
+5V: C6.1, J5.1, J6.8
+12V: J6.9
/32KHZ_CLK_REF: C4.1, U1.4 (PC14), Y2.2
/DIP_0: R13.2, U1.47 (PA15)
/DIP_1: R12.2, U1.48 (PC8)
/DIP_2: R11.2, U1.49 (PC9)
/DISPLAY_RX: J5.2, R9.2, U1.41 (PD9)
/DISPLAY_TX: J5.3, U1.40 (PD8)
/DISPLAY_~RST: J5.5, U1.42 (PA10/UCPD1_DBCC2)
/GPIO_PB3: J1.7, U1.57 (PB3)
/GPIO_PB4: J1.6, U1.58 (PB4)
/GPIO_PB5: J1.5, U1.59 (PB5)
/GPIO_PB6: J1.4, U1.60 (PB6)
/I2C_1_SCL: J1.2, R5.2, U1.62 (PB8)
/I2C_1_SDA: J1.3, R6.2, U1.61 (PB7)
/LED_BLUE_1: R1.1, U1.27 (PB0)
/LED_BLUE_2: R2.1, U1.30 (PB10)
/LED_GREEN: R3.1, U1.28 (PB1)
/LED_RED: R4.1, U1.29 (PB2)
/MCU_BOOT_BOOT0: J6.4, R10.2, R22.1
/MCU_BOOT_RST: J6.3, R20.1
/MCU_BOOT_RX: J6.6, R17.2, U1.20 (PA3)
/MCU_BOOT_TX: J6.5, R18.2, U1.19 (PA2)
/MCU_BOOT_~DET: J6.2, R19.2
/NRST: C8.1, J2.10 (~RESET), Q1.3 (D), SW3.2, U1.12 (PF2)
/OPTICAL_1_INT: J3.6, U1.25 (PC4)
/OPTICAL_1_MISO: J3.5, U1.23 (PA6)
/OPTICAL_1_MOSI: J3.4, U1.24 (PA7)
/OPTICAL_1_NSS: J3.2, U1.21 (PA4)
/OPTICAL_1_SCK: J3.3, U1.22 (PA5)
/OPTICAL_2_INT: J4.6, U1.37 (PA9/UCPD1_DBCC1)
/OPTICAL_2_MISO: J4.5, U1.34 (PB14)
/OPTICAL_2_MOSI: J4.4, U1.35 (PB15)
/OPTICAL_2_NSS: J4.2, U1.36 (PA8)
/OPTICAL_2_SCK: J4.3, U1.33 (PB13)
/SWCLK: J2.4 (SWDCLK/TCK), SW2.5, U1.46 (PA14)
/SWDIO: J2.2 (SWDIO/TMS), U1.45 (PA13)
/USER_ADJ1: RV1.2, U1.18 (PA1)
/USR_BTN: R7.1, U1.64 (PC10)
GND: C1.2, C2.2, C3.2, C4.2, C5.2, C6.2, C7.2, C8.2, C9.1, C10.1, C11.2, C12.2, D1.1 (K), D2.1 (K), D3.1 (K), D4.1 (K), J1.8, J2.3 (GND), J2.5 (GND), J2.9 (GNDDetect), J3.7, J3.MP (MountPin), J4.7, J4.MP (MountPin), J5.4, J5.MP (MountPin), J6.1, J6.MP (MountPin), Q1.2 (S), R8.2, R10.1, R14.1, R15.1, R16.1, R19.1, R21.2, RV1.3, SW3.1, U1.9 (VSS), Y1.2, Y1.4
unnamed: C3.1, R7.2, R8.1, SW1.1
unnamed: D1.2 (A), R1.2
unnamed: D2.2 (A), R2.2
unnamed: D3.2 (A), R3.2
unnamed: D4.2 (A), R4.2
unnamed: Q1.1 (G), R20.2, R21.1
unnamed: R11.1, R14.2, SW2.1
unnamed: R12.1, R15.2, SW2.2
unnamed: R13.1, R16.2, SW2.3
unnamed: R22.2, SW2.4
unnamed: C5.1, U1.5 (PC15), Y2.1
unnamed: C1.1, U1.10 (PF0), Y1.1
unnamed: C2.1, U1.11 (PF1), Y1.3

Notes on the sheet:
Peripherial Maps: BOOT: USART3 DISPLAY: USART2 OPTICAL_1: SPI1 OPTICAL_2: SPI2
Mounting Holes
Upstream MCU Connector
~{RST} has a pull-up on device side. Needs to be open-drain active low for 2us to reset.
Reset Logic
Software Indicators
To prevent garbage signal on boot-up
User Trim Pots
BOOT0 pin shares with SWCLK on G071xx. Refer to DIP Switch section.
Debug Header
STM32 has calibrated internal pull-up to sequence
Spare GPIO Connector
RX and TX are TTL, so 3.3V compatible.
User DIP SW
Upstream Power Input
User Button
Optical Flow Connectors (Designed for use with the Pimoroni PAA5100JE-Q Breakout board)
uC Decoupling
Display Connector (Designed for use with the 4D Systems uLCD-144G2 LCD Breakout Board)
Note: Control board will label as ~{RST}, but open-drain method requires active high. Will have active high in code on Control.
Microcontroller

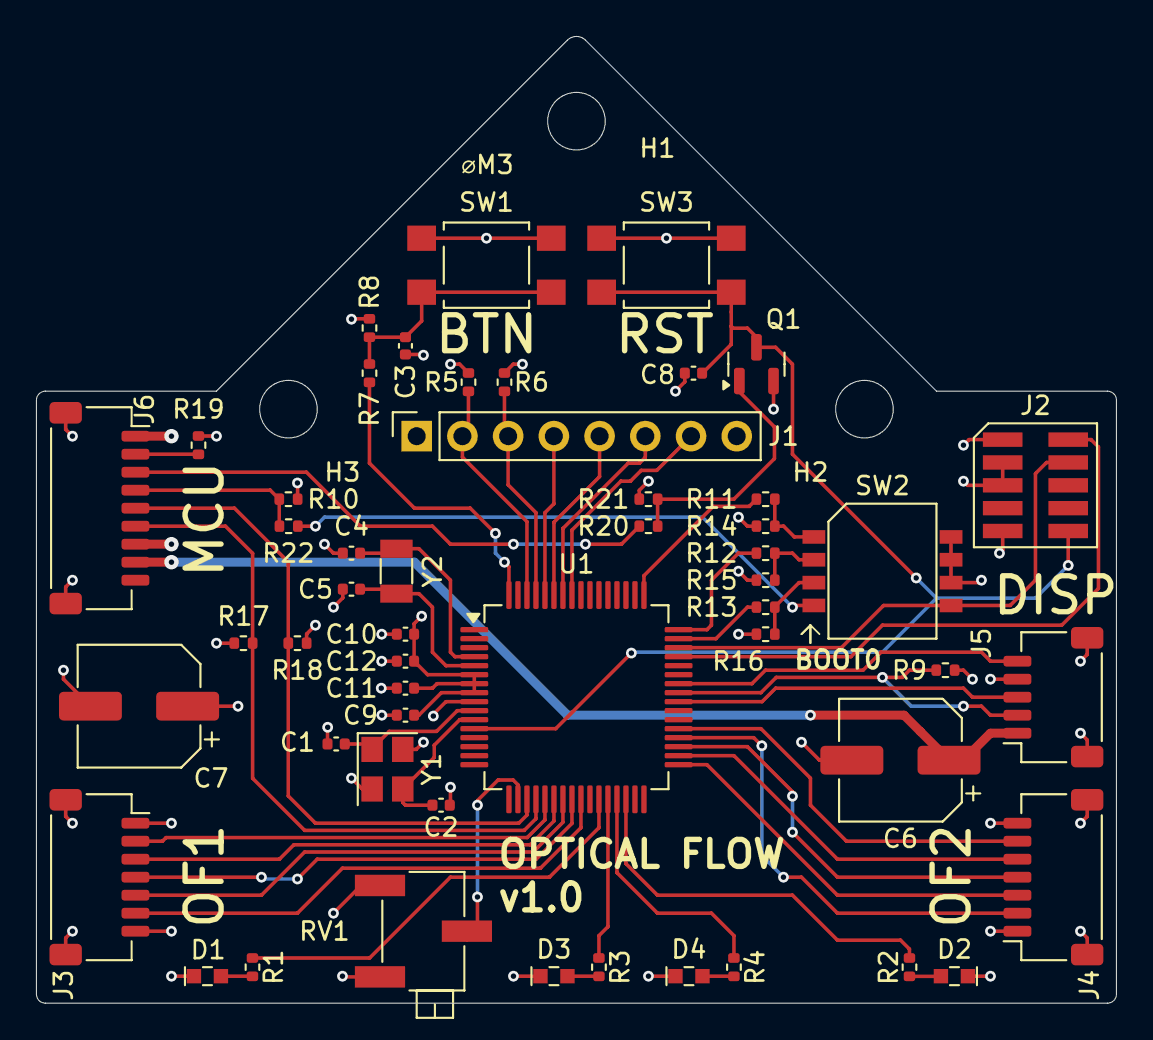
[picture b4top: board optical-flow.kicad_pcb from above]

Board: 4 copper layers, 60.0 x 53.7 mm, 55 parts (0 on the bottom side), 53 nets.
